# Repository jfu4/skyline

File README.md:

# skyline keyboard

A 54-key split, reversible keyboard powered by the nRF52840 (Holyiot module).  
Features:
- 15x white backlight LEDs  
- nice!view LCD  
- 700mAh LiPo battery (planned)  
- Encoder support (2 optional switches)  

Designed in KiCad.

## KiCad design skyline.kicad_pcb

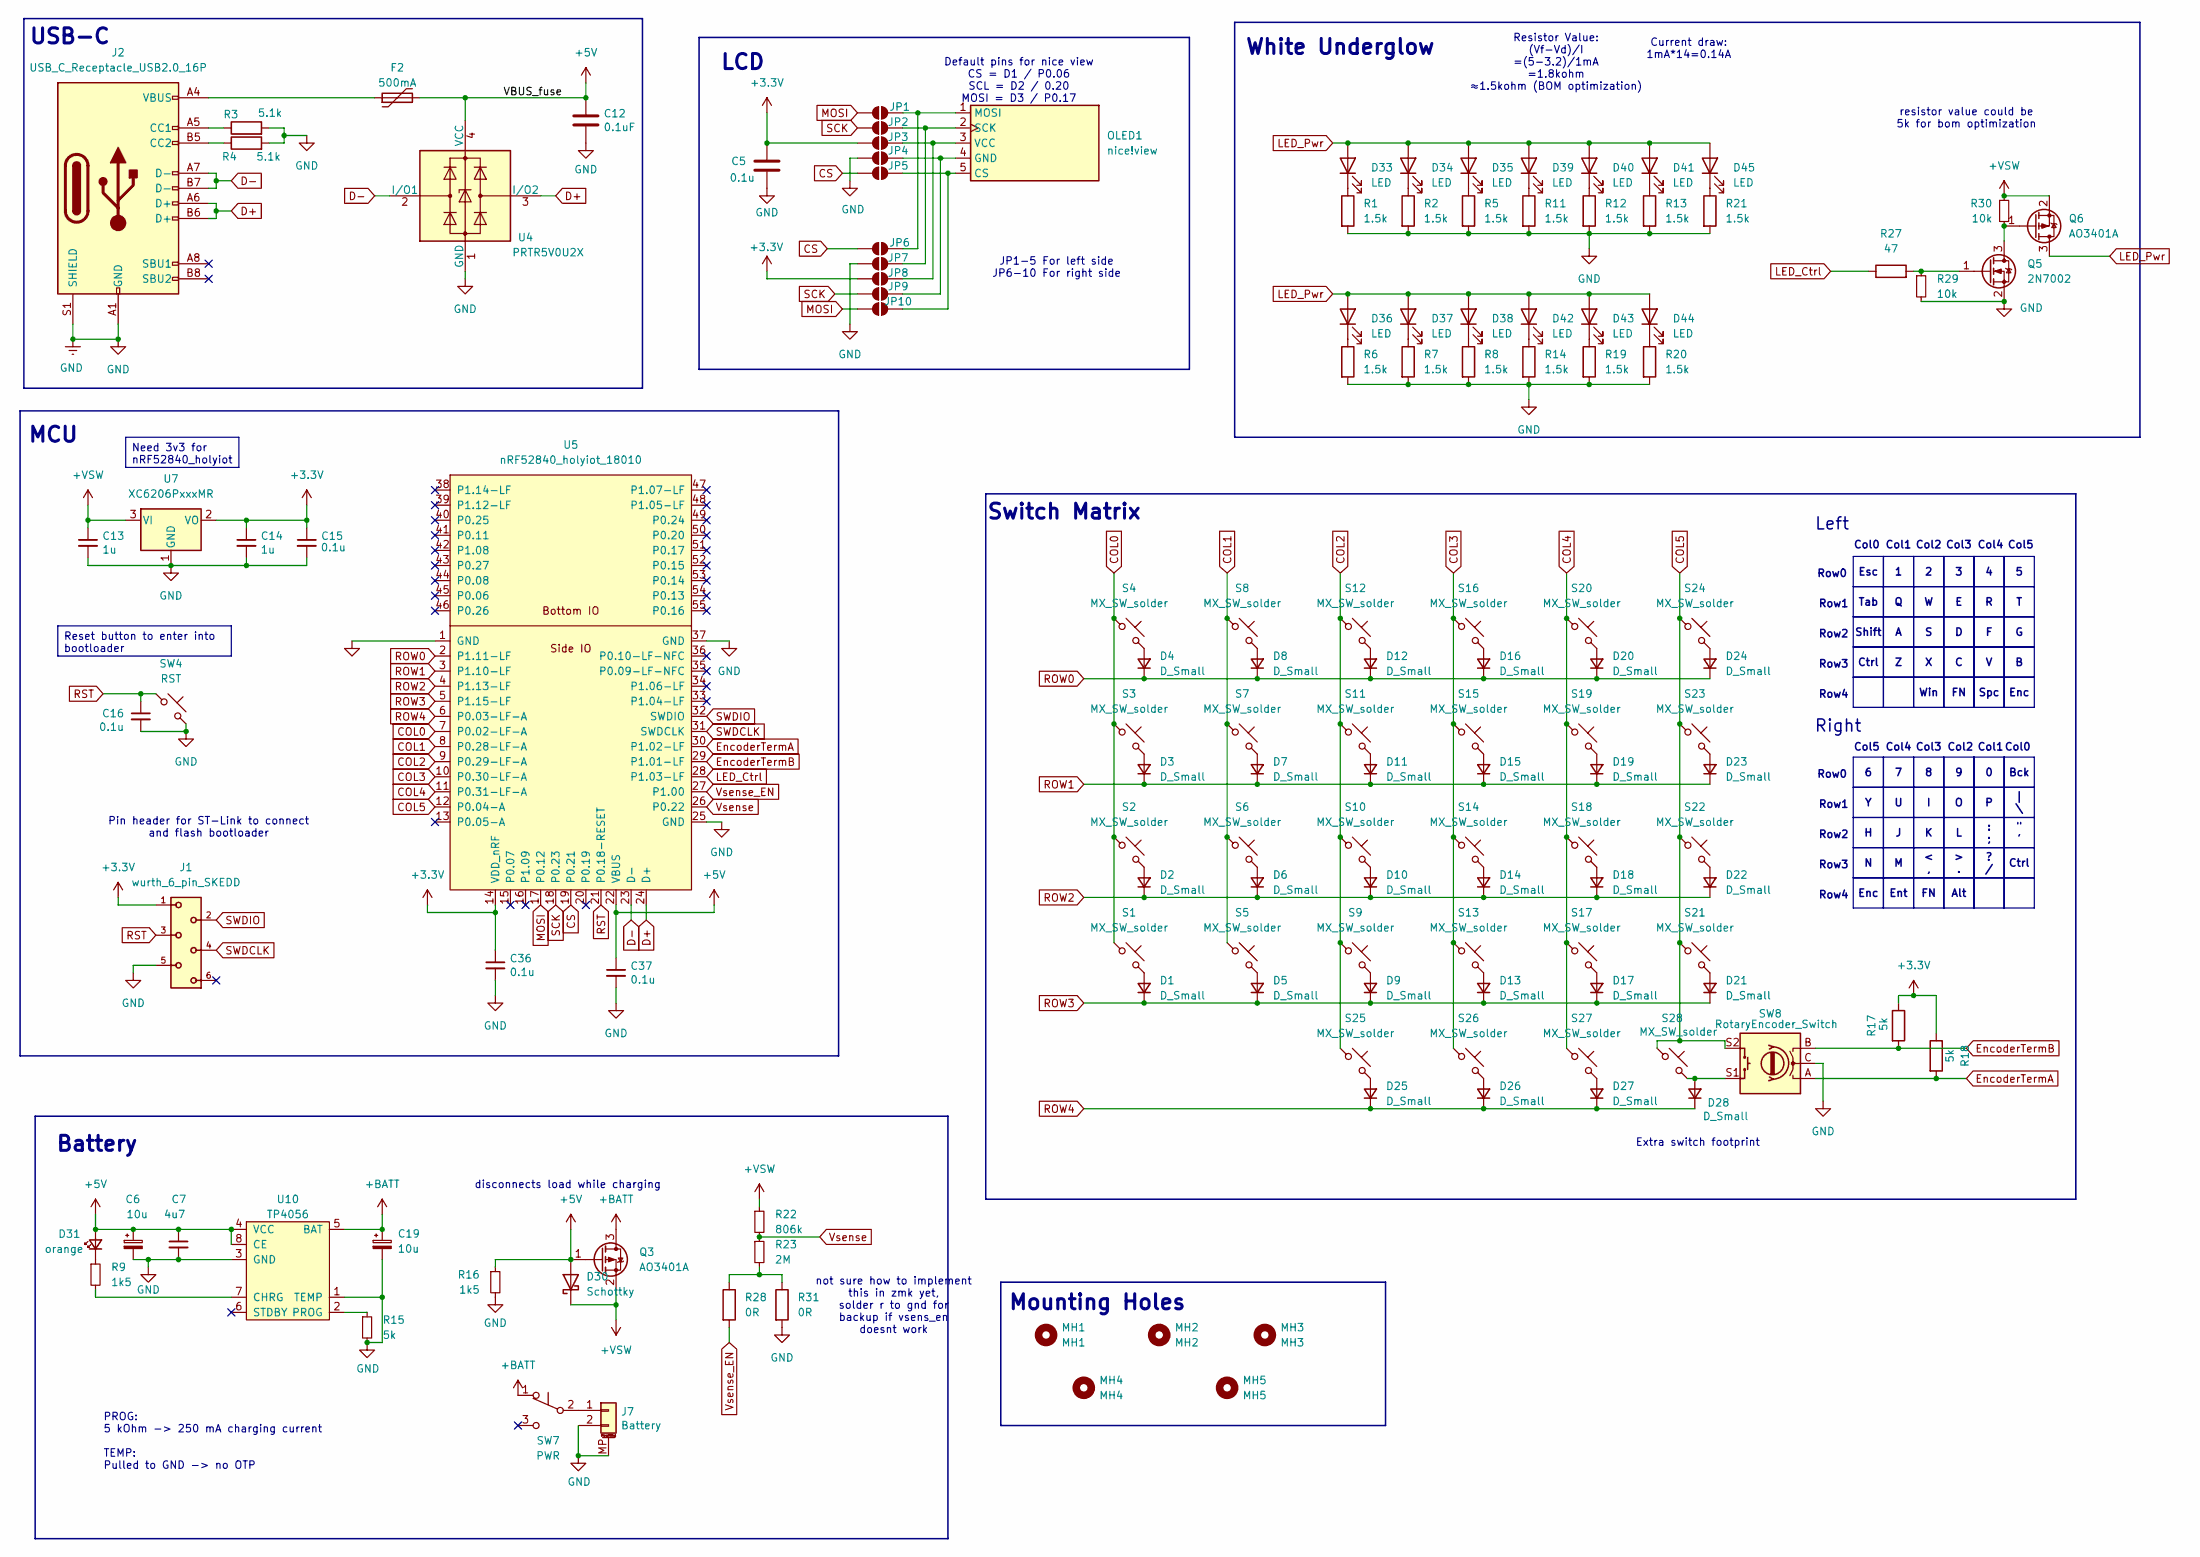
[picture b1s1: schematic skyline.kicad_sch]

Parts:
C5, C15, C16, C36, C37: 0.1u; C_0805_2012Metric_Pad1.18x1.45mm_HandSolder
C6, C19: 10u; CP_EIA-3216-18_Kemet-A_Pad1.58x1.35mm_HandSolder
C7: 4u7; C_0805_2012Metric_Pad1.18x1.45mm_HandSolder
C12: 0.1uF; C_0805_2012Metric_Pad1.18x1.45mm_HandSolder; LCSC C307331
C13, C14: 1u; C_0805_2012Metric_Pad1.18x1.45mm_HandSolder
D1, D2, D3, D4, D5, D6, D7, D8, D9, D10, D11, D12, D13, D14, D15, D16, D17, D18, D19, D20, D21, D22, D23, D24, D25, D26, D27, D28: D_Small; D_0805_2012Metric_Pad1.15x1.40mm_HandSolder
D30: Schottky; D_SOD-123
D31: orange; LED_0402_1005Metric_Pad0.77x0.64mm_HandSolder
D33, D34, D35, D36, D37, D38, D39, D40, D41, D42, D43, D44, D45: LED; reversible_D_0805_2012Metric_Pad1.15x1.40mm_HandSolder
F2: 500mA; Fuse_1206_3216Metric; LCSC C135341
J1: wurth_6_pin_SKEDD
J2: USB_C_Receptacle_USB2.0_16P; USB_C_Receptacle_HRO_TYPE-C-31-M-12_reversible
J7: Battery; reversible_Molex_Pico-EZmate_78171-0002_1x02-1MP_P1.20mm_Ve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; LCSC C505023
JP1, JP2, JP3, JP4, JP5, JP6, JP7, JP8, JP9, JP10: SolderJumper_2_Open; Jumper_solder
MH1: MH1; mounting_hole_npth
MH2: MH2; mounting_hole_npth
MH3: MH3; mounting_hole_npth
MH4: MH4; mounting_hole_npth
MH5: MH5; mounting_hole_npth
OLED1: nice!view; nice_view
Q3, Q6: AO3401A; SOT-23
Q5: 2N7002; SOT-23
R1, R2, R5, R6, R7, R8, R11, R12, R13, R14, R19, R20, R21: 1.5k; R_0805_2012Metric_Pad1.20x1.40mm_HandSolder
R3, R4: 5.1k; R_0805_2012Metric_Pad1.20x1.40mm_HandSolder
R9, R16: 1k5; R_0805_2012Metric_Pad1.20x1.40mm_HandSolder
R15, R17, R18: 5k; R_0805_2012Metric_Pad1.20x1.40mm_HandSolder
R22: 806k; R_0805_2012Metric_Pad1.20x1.40mm_HandSolder
R23: 2M; R_0805_2012Metric_Pad1.20x1.40mm_HandSolder
R27: 47; R_0805_2012Metric_Pad1.20x1.40mm_HandSolder
R28, R31: 0R; R_0805_2012Metric_Pad1.20x1.40mm_HandSolder
R29, R30: 10k; R_0805_2012Metric_Pad1.20x1.40mm_HandSolder
S1, S2, S3, S4, S5, S6, S7, S8, S9, S10, S11, S12, S13, S14, S15, S16, S17, S18, S19, S20, S21, S22, S23, S24, S25, S26, S27, S28: MX_SW_solder; SW_MX_Reversible_1u
SW4: RST; reversible_SW_SPST_SKQG_WithStem
SW7: PWR; reversible_SW_MSK12C02-HB
SW8: RotaryEncoder_Switch; ROT_Alps_EC11E-Switch
U4: PRTR5V0U2X; SOT-143; LCSC C2827688
U5: nRF52840_holyiot_18010; nRF52840_holyiot_18010_HS_simple_reversible
U7: XC6206PxxxMR; SOT-23
U10: TP4056; SOP-8-1EP_4.57x4.57mm_P1.27mm_EP4.57x4.45mm; LCSC C16581

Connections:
+3.3V: C5.1, C14.1, C15.1, C36.1, J1.1, JP3.1 (A), JP8.1 (A), R17.1, R18.1, U5.14 (VDD_nRF), U7.2 (VO)
+5V: C6.1, C7.1, C12.1, C37.1, D30.2 (A), D31.2 (A), F2.2, Q3.1 (G), R16.1, U4.4 (VCC), U5.22 (VBUS), U10.4 (VCC), U10.8 (CE)
+BATT: C19.1, Q3.3 (D), SW7.1 (A), U10.5 (BAT)
+VSW: C13.1, D30.1 (K), Q3.2 (S), Q6.2 (S), R22.1, R30.1, U7.3 (VI)
COL0: S1.1, S2.1, S3.1, S4.1, U5.7 (P0.02-LF-A)
COL1: S5.1, S6.1, S7.1, S8.1, U5.8 (P0.28-LF-A)
COL2: S9.1, S10.1, S11.1, S12.1, S25.1, U5.9 (P0.29-LF-A)
COL3: S13.1, S14.1, S15.1, S16.1, S26.1, U5.10 (P0.30-LF-A)
COL4: S17.1, S18.1, S19.1, S20.1, S27.1, U5.11 (P0.31-LF-A)
COL5: S21.1, S22.1, S23.1, S24.1, S28.1, SW8.S2, U5.12 (P0.04-A)
CS: JP5.1 (A), JP6.1 (A), U5.19 (P0.21)
D+: J2.A6 (D+), J2.B6 (D+), U4.3 (I/O2), U5.24 (D+)
D-: J2.A7 (D-), J2.B7 (D-), U4.2 (I/O1), U5.23 (D-)
EncoderTermA: R18.2, SW8.A, U5.30 (P1.02-LF)
EncoderTermB: R17.2, SW8.B, U5.29 (P1.01-LF)
GND: C5.2, C6.2, C7.2, C12.2, C13.2, C14.2, C15.2, C16.2, C19.2, C36.2, C37.2, J1.5, J2.A1 (GND), J2.A12 (GND), J2.B1 (GND), J2.B12 (GND), J2.S1 (SHIELD), J7.2, J7.MP (MountPin), JP4.1 (A), JP7.1 (A), Q5.2 (S), R1.2, R2.2, R3.2, R4.2, R5.2, R6.2, R7.2, R8.2, R11.2, R12.2, R13.2, R14.2, R15.2, R16.2, R19.2, R20.2, R21.2, R29.2, R31.2, SW4.2, SW8.C, U4.1 (GND), U5.1 (GND), U5.25 (GND), U5.37 (GND), U7.1 (GND), U10.1 (TEMP), U10.3 (GND)
LED_Ctrl: R27.1, U5.28 (P1.03-LF)
LED_Pwr: D33.2 (A), D34.2 (A), D35.2 (A), D36.2 (A), D37.2 (A), D38.2 (A), D39.2 (A), D40.2 (A), D41.2 (A), D42.2 (A), D43.2 (A), D44.2 (A), D45.2 (A), Q6.3 (D)
MOSI: JP1.1 (A), JP10.1 (A), U5.17 (P0.12)
unnamed: D1.2 (A), S1.2
unnamed: D2.2 (A), S2.2
unnamed: D3.2 (A), S3.2
unnamed: D4.2 (A), S4.2
unnamed: D5.2 (A), S5.2
unnamed: D6.2 (A), S6.2
unnamed: D7.2 (A), S7.2
unnamed: D8.2 (A), S8.2
unnamed: D9.2 (A), S9.2
unnamed: D10.2 (A), S10.2
unnamed: D11.2 (A), S11.2
unnamed: D12.2 (A), S12.2
unnamed: D13.2 (A), S13.2
unnamed: D14.2 (A), S14.2
unnamed: D15.2 (A), S15.2
unnamed: D16.2 (A), S16.2
unnamed: D17.2 (A), S17.2
unnamed: D18.2 (A), S18.2
unnamed: D19.2 (A), S19.2
unnamed: D20.2 (A), S20.2
unnamed: D21.2 (A), S21.2
unnamed: D22.2 (A), S22.2
unnamed: D23.2 (A), S23.2
unnamed: D24.2 (A), S24.2
unnamed: D25.2 (A), S25.2
unnamed: D26.2 (A), S26.2
unnamed: D27.2 (A), S27.2
unnamed: D28.2 (A), S28.2, SW8.S1
unnamed: D31.1 (K), R9.1
unnamed: D33.1 (K), R1.1
unnamed: D34.1 (K), R2.1
unnamed: D35.1 (K), R5.1
unnamed: D36.1 (K), R6.1
unnamed: D37.1 (K), R7.1
unnamed: D38.1 (K), R8.1
unnamed: D39.1 (K), R11.1
unnamed: D40.1 (K), R12.1
unnamed: D41.1 (K), R13.1
unnamed: D42.1 (K), R14.1
unnamed: D43.1 (K), R19.1
unnamed: D44.1 (K), R20.1
unnamed: D45.1 (K), R21.1
unnamed: F2.1, J2.A4 (VBUS), J2.A9 (VBUS), J2.B4 (VBUS), J2.B9 (VBUS)
unnamed: J2.A5 (CC1), R3.1
unnamed: J2.B5 (CC2), R4.1
unnamed: J7.1, SW7.2 (B)
unnamed: JP1.2 (B), JP6.2 (B), OLED1.1 (MOSI)
unnamed: JP2.2 (B), JP7.2 (B), OLED1.2 (SCK)
unnamed: JP3.2 (B), JP8.2 (B), OLED1.3 (VCC)
unnamed: JP4.2 (B), JP9.2 (B), OLED1.4 (GND)
unnamed: JP5.2 (B), JP10.2 (B), OLED1.5 (CS)
unnamed: Q5.3 (D), Q6.1 (G), R30.2
unnamed: Q5.1 (G), R27.2, R29.1
unnamed: R23.2, R28.1, R31.1
unnamed: R9.2, U10.7 (CHRG)
unnamed: R15.1, U10.2 (PROG)
ROW0: D4.1 (K), D8.1 (K), D12.1 (K), D16.1 (K), D20.1 (K), D24.1 (K), U5.2 (P1.11-LF)
ROW1: D3.1 (K), D7.1 (K), D11.1 (K), D15.1 (K), D19.1 (K), D23.1 (K), U5.3 (P1.10-LF)
ROW2: D2.1 (K), D6.1 (K), D10.1 (K), D14.1 (K), D18.1 (K), D22.1 (K), U5.4 (P1.13-LF)
ROW3: D1.1 (K), D5.1 (K), D9.1 (K), D13.1 (K), D17.1 (K), D21.1 (K), U5.5 (P1.15-LF)
ROW4: D25.1 (K), D26.1 (K), D27.1 (K), D28.1 (K), U5.6 (P0.03-LF-A)
RST: C16.1, J1.3, SW4.1, U5.21 (P0.18-RESET)
SCK: JP2.1 (A), JP9.1 (A), U5.18 (P0.23)
SWDCLK: J1.4, U5.31 (SWDCLK)
SWDIO: J1.2, U5.32 (SWDIO)
Vsense: R22.2, R23.1, U5.26 (P0.22)
Vsense_EN: R28.2, U5.27 (P1.00)

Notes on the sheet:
Mounting Holes
Switch Matrix
JP1-5 For left side JP6-10 For right side
> .
Col0
Row2
Spc
Current draw: 1mA*14=0.14A
Col2
Ctrl
Tab
Battery
Row4
Row1
Row3
Shift
Row0
Bck
disconnects load while charging
Right
| \
White Underglow
? /
Esc
PROG: 5 kOhm -> 250 mA charging current TEMP: Pulled to GND -> no OTP
Col3
: ;
Col4
Enc
Col5
< ,
LCD
MCU
resistor value could be 5k for bom optimization
Col1
Ent
Pin header for ST-Link to connect and flash bootloader
Win
" '
Left

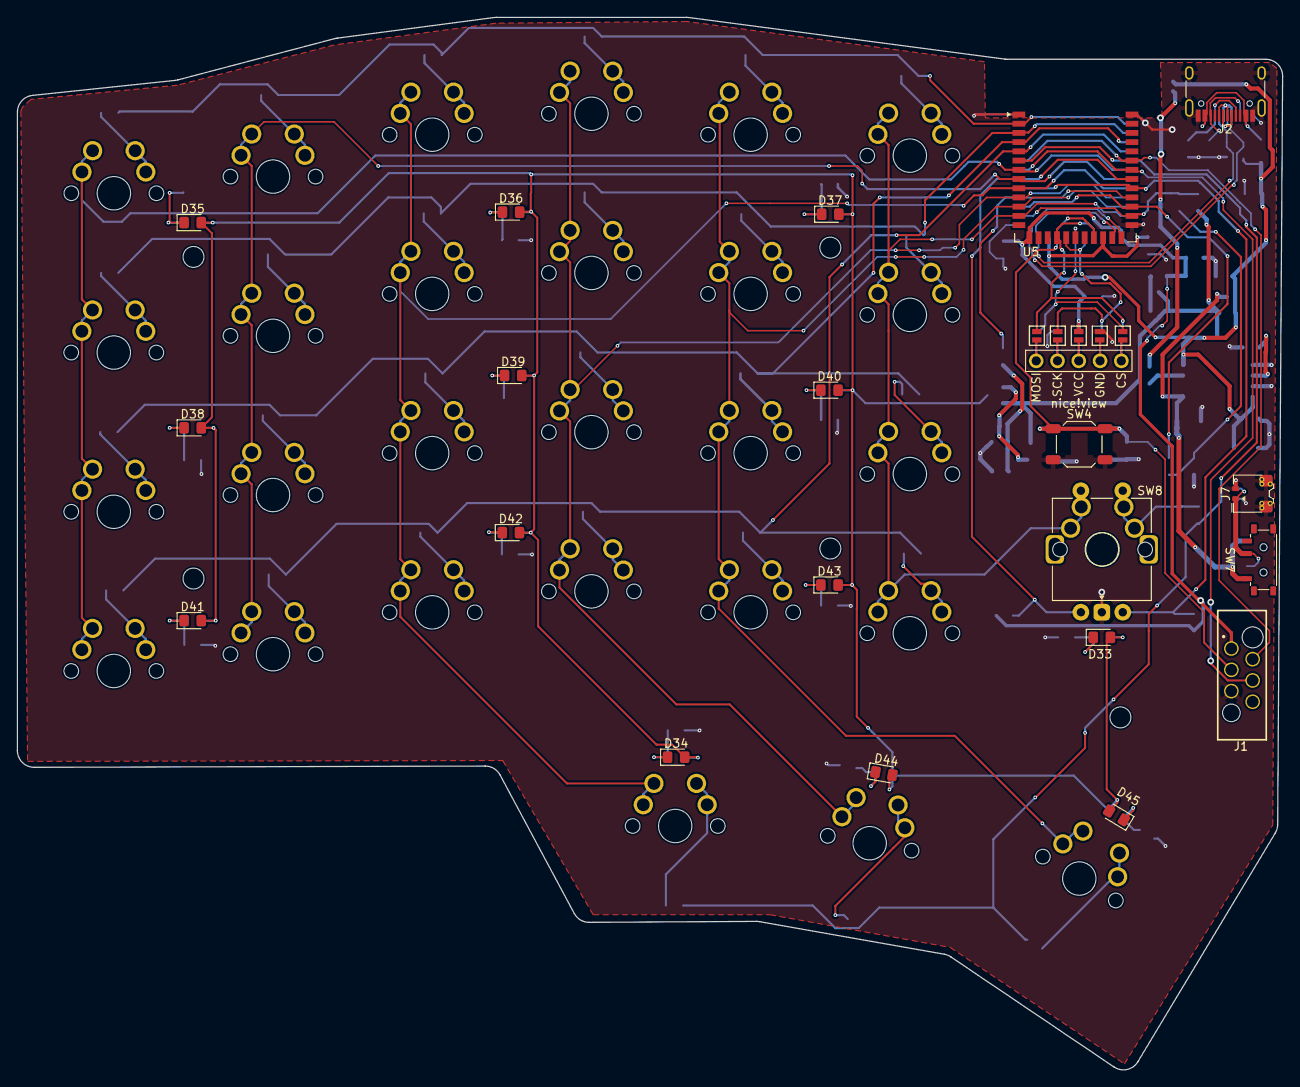
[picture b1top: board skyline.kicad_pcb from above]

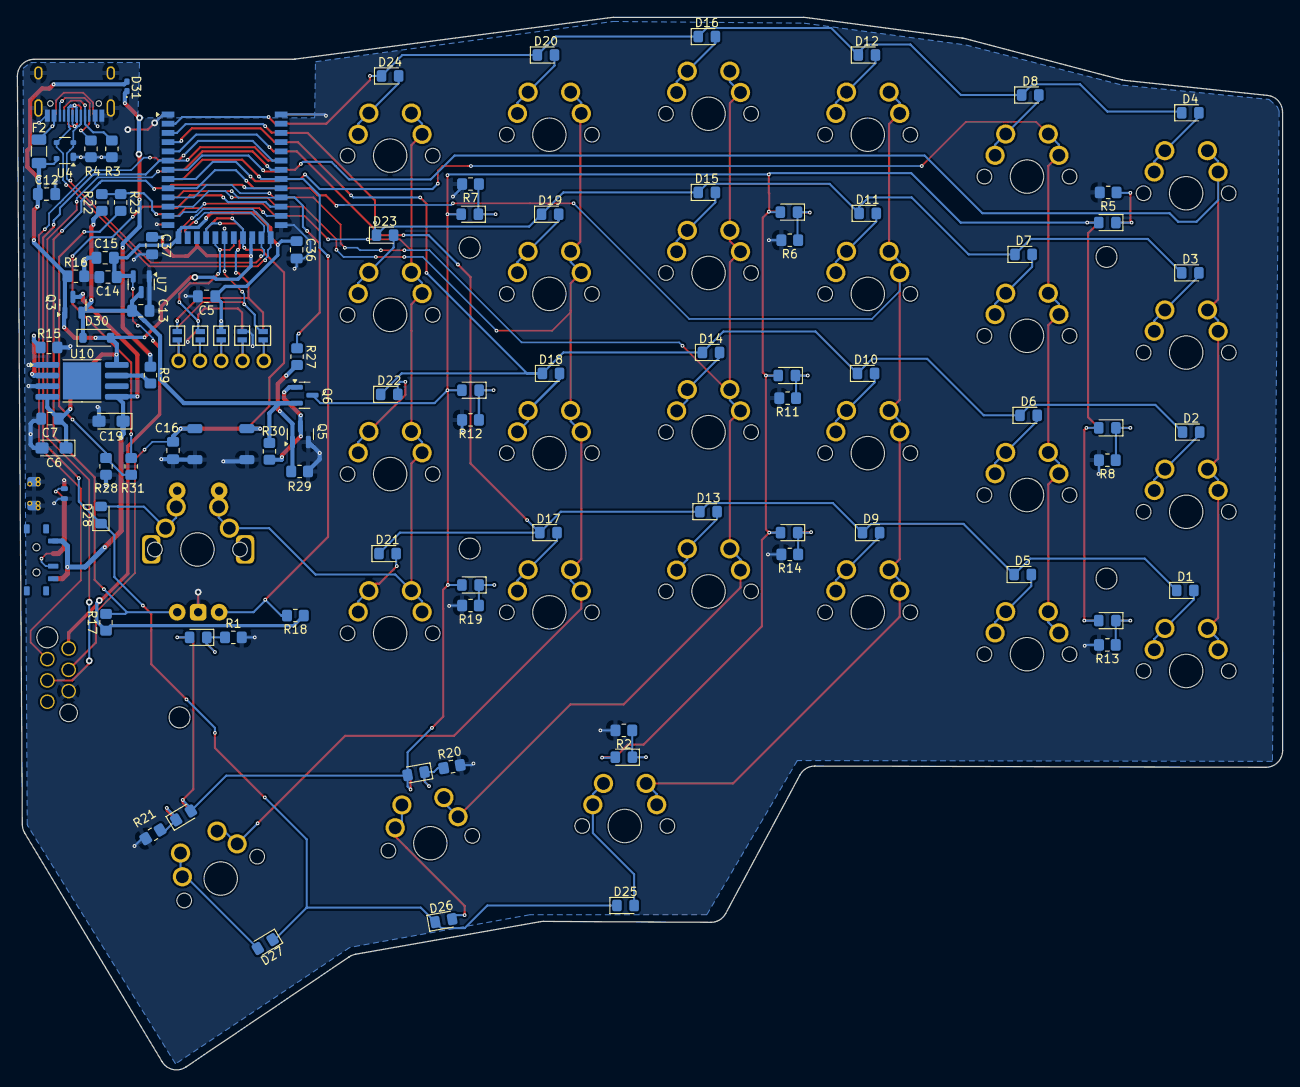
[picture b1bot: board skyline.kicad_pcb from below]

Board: 2 copper layers, 151.0 x 125.6 mm, 139 parts (80 on the bottom side), 86 nets.

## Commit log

2025-10-10 Initial commit of existing KiCad Project
2025-10-10 Add KiCad .gitignore
2025-10-10 Add README
2025-10-10 Removed files pt 2
2025-10-12 Added rev. led footprints, jumpers for niceview
2025-10-29 finished routing, need to fix it up now
2025-10-30 finished routing, need to review
2025-10-30 deleted left and right schematics, just main now
